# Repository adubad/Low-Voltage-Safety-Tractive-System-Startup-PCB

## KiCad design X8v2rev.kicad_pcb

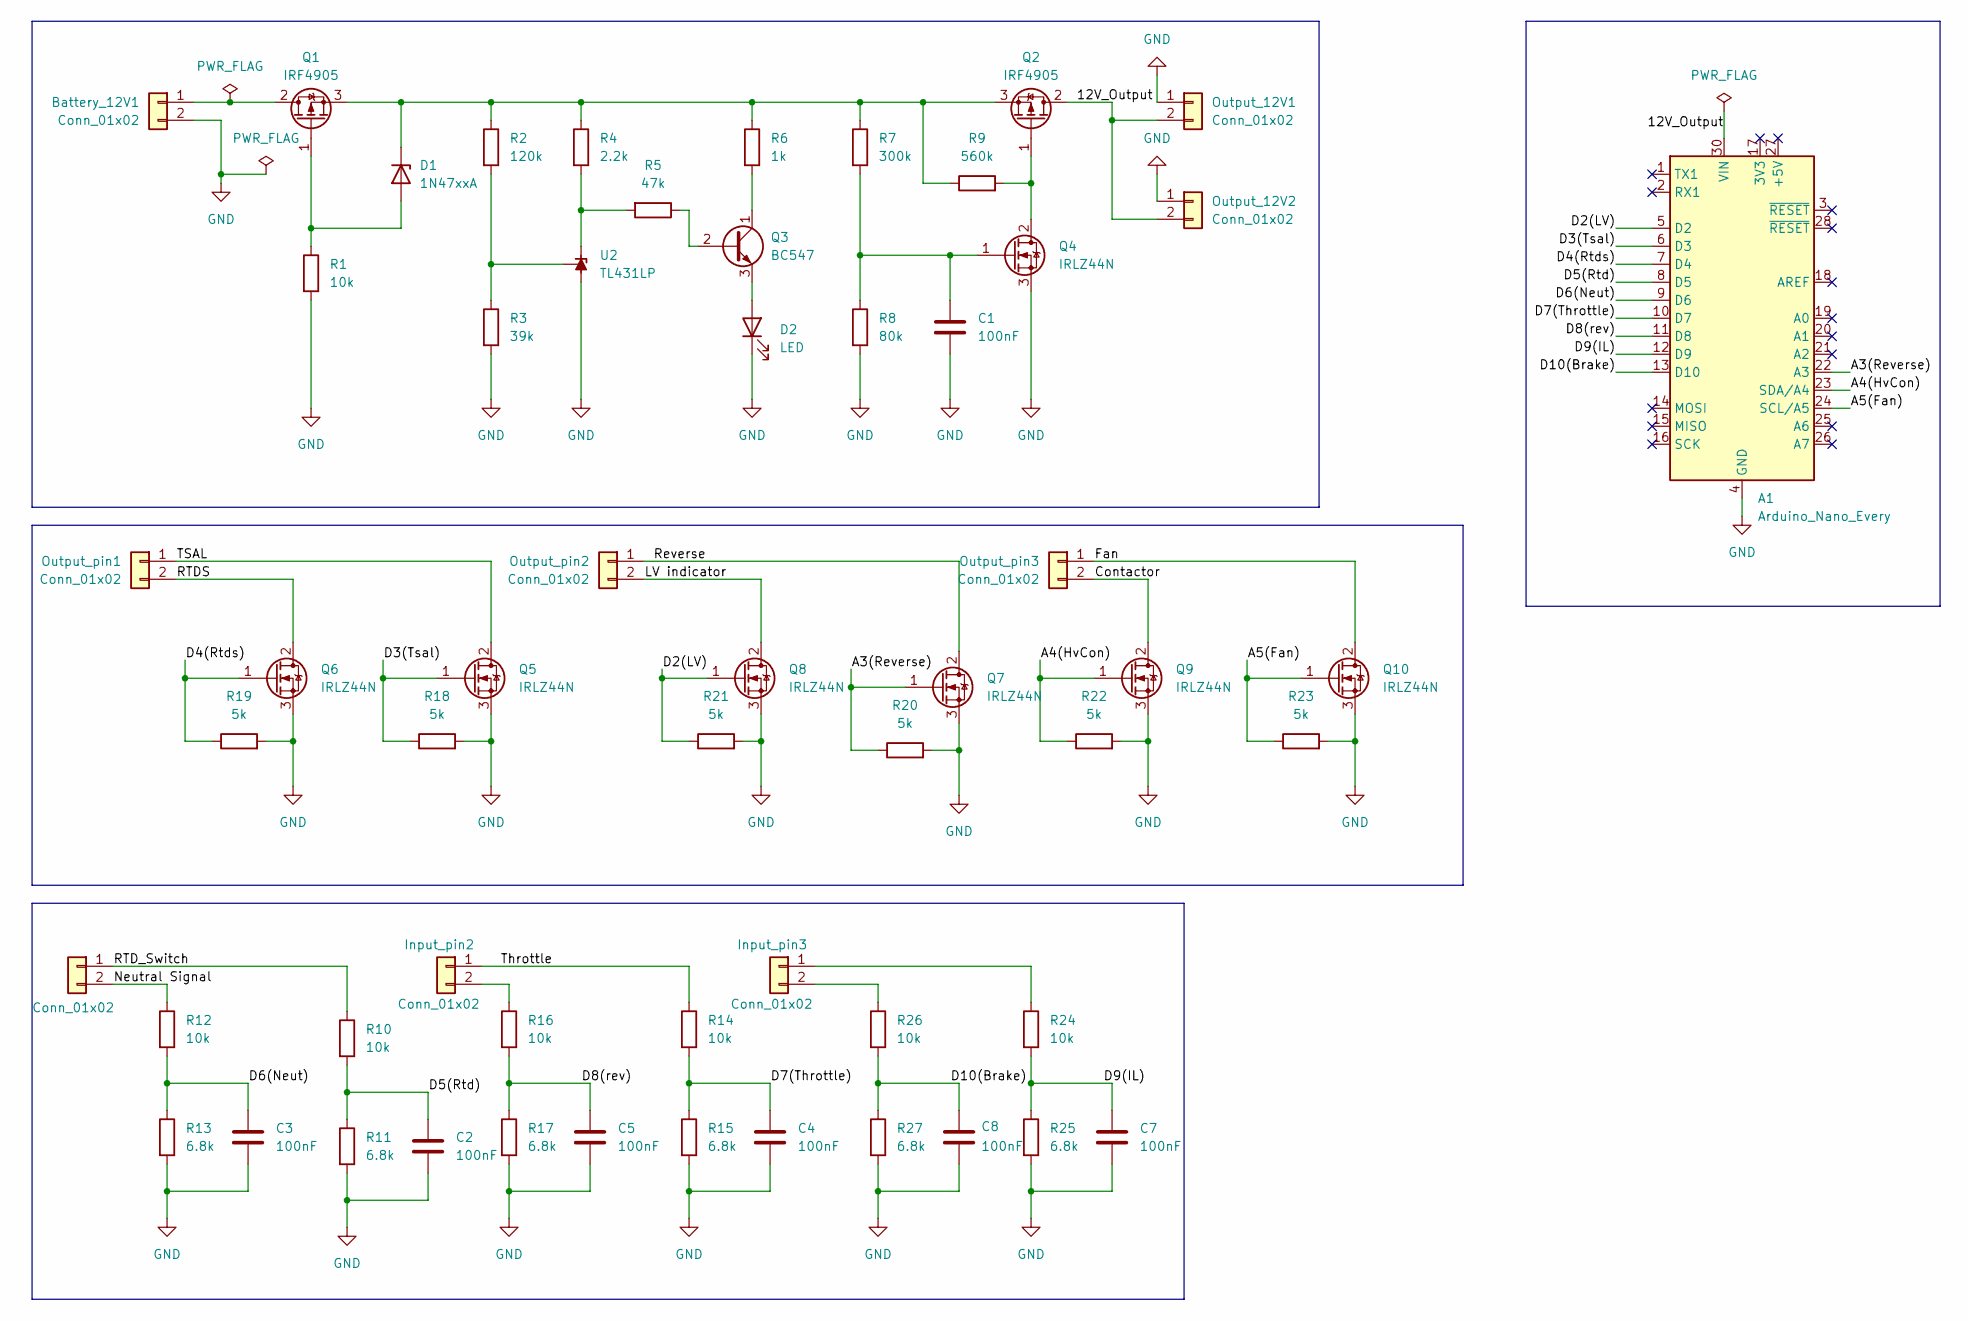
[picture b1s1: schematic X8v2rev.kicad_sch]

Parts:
A1: Arduino_Nano_Every; Arduino_Nano
Battery_12V1: Conn_01x02; TerminalBlock_Phoenix_MKDS-1,5-2_1x02_P5.00mm_Horizontal
C1, C2, C3, C4, C5, C7, C8: 100nF; C_Disc_D5.0mm_W2.5mm_P5.00mm
D1: 1N47xxA; D_DO-41_SOD81_P10.16mm_Horizontal
D2: LED; LED_D3.0mm
Input_pin1, Input_pin2, Input_pin3: Conn_01x02; TerminalBlock_Phoenix_MKDS-1,5-2_1x02_P5.00mm_Horizontal
Output_12V1, Output_12V2: Conn_01x02; TerminalBlock_Phoenix_MKDS-1,5-2_1x02_P5.00mm_Horizontal
Output_pin1, Output_pin2, Output_pin3: Conn_01x02; TerminalBlock_Phoenix_MKDS-1,5-2_1x02_P5.00mm_Horizontal
Q1, Q2: IRF4905; TO-220-3_Vertical
Q3: BC547; TO-92_Inline
Q4, Q5, Q6, Q7, Q8, Q9, Q10: IRLZ44N; TO-220-3_Vertical
R1, R10, R12, R14, R16, R24, R26: 10k; R_Axial_DIN0207_L6.3mm_D2.5mm_P10.16mm_Horizontal
R2: 120k; R_Axial_DIN0207_L6.3mm_D2.5mm_P10.16mm_Horizontal
R3: 39k; R_Axial_DIN0207_L6.3mm_D2.5mm_P10.16mm_Horizontal
R4: 2.2k; R_Axial_DIN0207_L6.3mm_D2.5mm_P10.16mm_Horizontal
R5: 47k; R_Axial_DIN0207_L6.3mm_D2.5mm_P10.16mm_Horizontal
R6: 1k; R_Axial_DIN0207_L6.3mm_D2.5mm_P10.16mm_Horizontal
R7: 300k; R_Axial_DIN0207_L6.3mm_D2.5mm_P10.16mm_Horizontal
R8: 80k; R_Axial_DIN0207_L6.3mm_D2.5mm_P10.16mm_Horizontal
R9: 560k; R_Axial_DIN0207_L6.3mm_D2.5mm_P10.16mm_Horizontal
R11, R13, R15, R17, R25, R27: 6.8k; R_Axial_DIN0207_L6.3mm_D2.5mm_P10.16mm_Horizontal
R18, R19, R20, R21, R22, R23: 5k; R_Axial_DIN0207_L6.3mm_D2.5mm_P10.16mm_Horizontal
U2: TL431LP; TO-92_Inline

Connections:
/12V_Output: A1.30 (VIN), Output_12V1.2, Output_12V2.2, Q2.2 (D)
/ LV indicator: Output_pin2.2, Q8.2 (D)
/A3(Reverse): A1.22 (A3), Q7.1 (G), R20.1
/A4(HvCon): A1.23 (SDA/A4), Q9.1 (G), R22.1
/A5(Fan): A1.24 (SCL/A5), Q10.1 (G), R23.1
/Contactor: Output_pin3.2, Q9.2 (D)
/D2(LV): A1.5 (D2), Q8.1 (G), R21.1
/D3(Tsal): A1.6 (D3), Q5.1 (G), R18.1
/D4(Rtds): A1.7 (D4), Q6.1 (G), R19.1
/D5(Rtd): A1.8 (D5), C2.1, R10.2, R11.1
/D6(Neut): A1.9 (D6), C3.1, R12.2, R13.1
/D7(Throttle): A1.10 (D7), C4.1, R14.2, R15.1
/D8(rev): A1.11 (D8), C5.1, R16.2, R17.1
/D9(IL): A1.12 (D9), C7.1, R24.2, R25.1
/D10(Brake): A1.13 (D10), C8.1, R26.2, R27.1
/Fan: Output_pin3.1, Q10.2 (D)
/Neutral Signal: Input_pin1.2, R12.1
/RTDS: Output_pin1.2, Q6.2 (D)
/RTD_Switch: Input_pin1.1, R10.1
/Reverse: Output_pin2.1, Q7.2 (D)
/TSAL: Output_pin1.1, Q5.2 (D)
/Throttle: Input_pin2.1, R14.1
GND: A1.4 (GND), A1.29 (GND), Battery_12V1.2, C1.2, C2.2, C3.2, C4.2, C5.2, C7.2, C8.2, D2.1 (K), Output_12V1.1, Output_12V2.1, Q4.3 (S), Q5.3 (S), Q6.3 (S), Q7.3 (S), Q8.3 (S), Q9.3 (S), Q10.3 (S), R1.2, R3.2, R8.2, R11.2, R13.2, R15.2, R17.2, R18.2, R19.2, R20.2, R21.2, R22.2, R23.2, R25.2, R27.2, U2.2 (A)
unnamed: Battery_12V1.1, Q1.2 (D)
unnamed: D1.2 (A), Q1.1 (G), R1.1
unnamed: D1.1 (K), Q1.3 (S), Q2.3 (S), R2.1, R4.1, R6.1, R7.1, R9.1
unnamed: D2.2 (A), Q3.3 (E)
unnamed: Input_pin2.2, R16.1
unnamed: Input_pin3.1, R24.1
unnamed: Input_pin3.2, R26.1
unnamed: Q2.1 (G), Q4.2 (D), R9.2
unnamed: Q3.2 (B), R5.1
unnamed: Q3.1 (C), R6.2
unnamed: C1.1, Q4.1 (G), R7.2, R8.1
unnamed: R4.2, R5.2, U2.3 (K)
unnamed: R2.2, R3.1, U2.1 (REF)

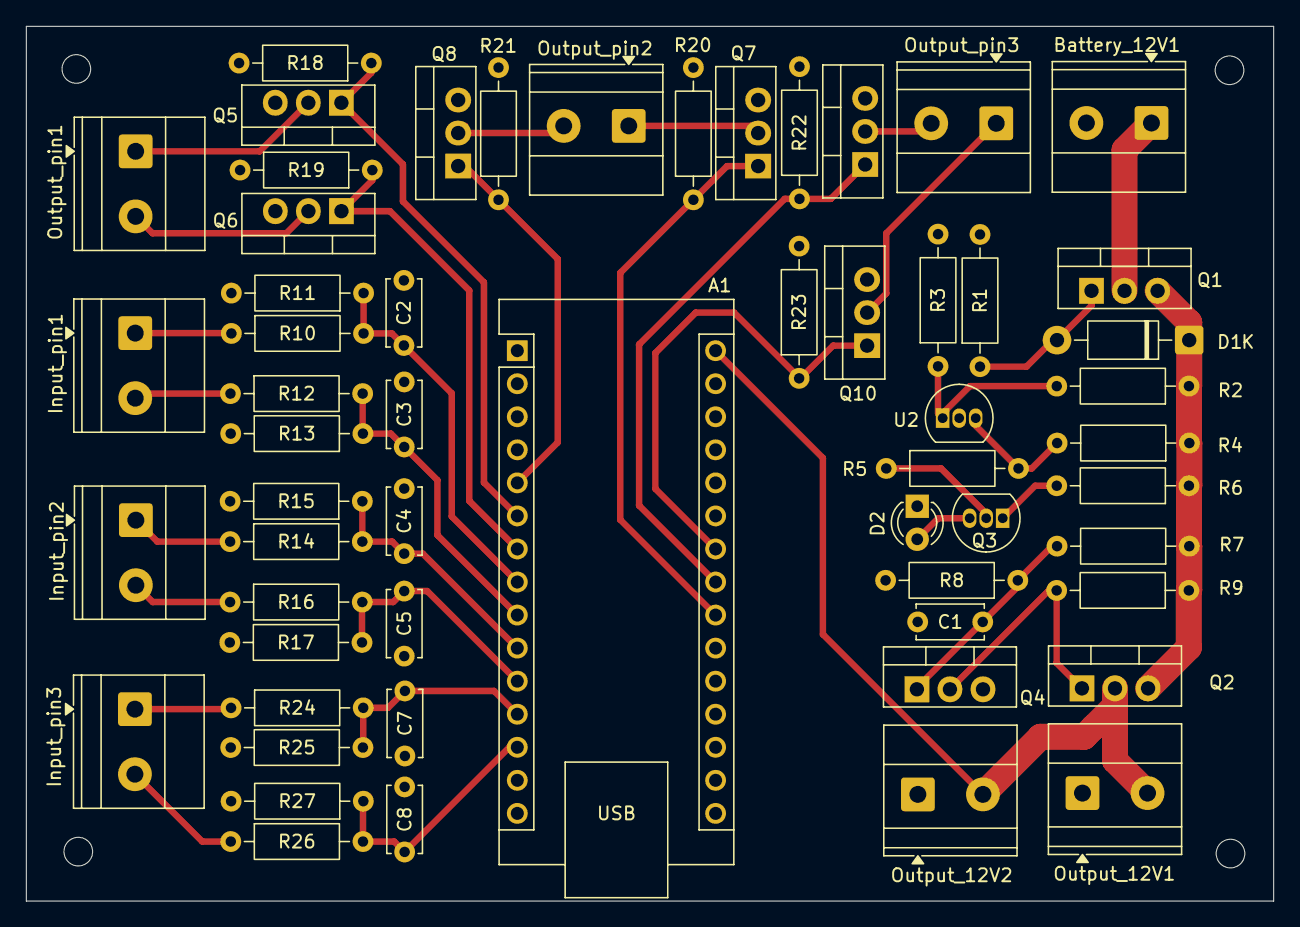
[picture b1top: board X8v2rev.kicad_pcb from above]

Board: 2 copper layers, 95.9 x 67.2 mm, 57 parts (0 on the bottom side), 36 nets.

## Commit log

2026-06-30 Initial Project Upload
    PCB design Of Safety Circuit and Startup circuit.
